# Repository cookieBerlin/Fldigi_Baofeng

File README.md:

# Fldigi_Baofeng
Interface between PC and a Baofeng

Sources:
- Speaker Microphone Pin Out http://www.miklor.com/COM/UV_Technical.php
- NBEMS using a Baofeng UV-5R on the cheap http://imnota.xenopho.be/2013/09/nbems-using-baofeng-uv-5r-on-cheap.html
- schematic of my simple audio interface for the UV-3R and UV-5R https://www.nonstopsystems.com/radio/hellschreiber-software.htm

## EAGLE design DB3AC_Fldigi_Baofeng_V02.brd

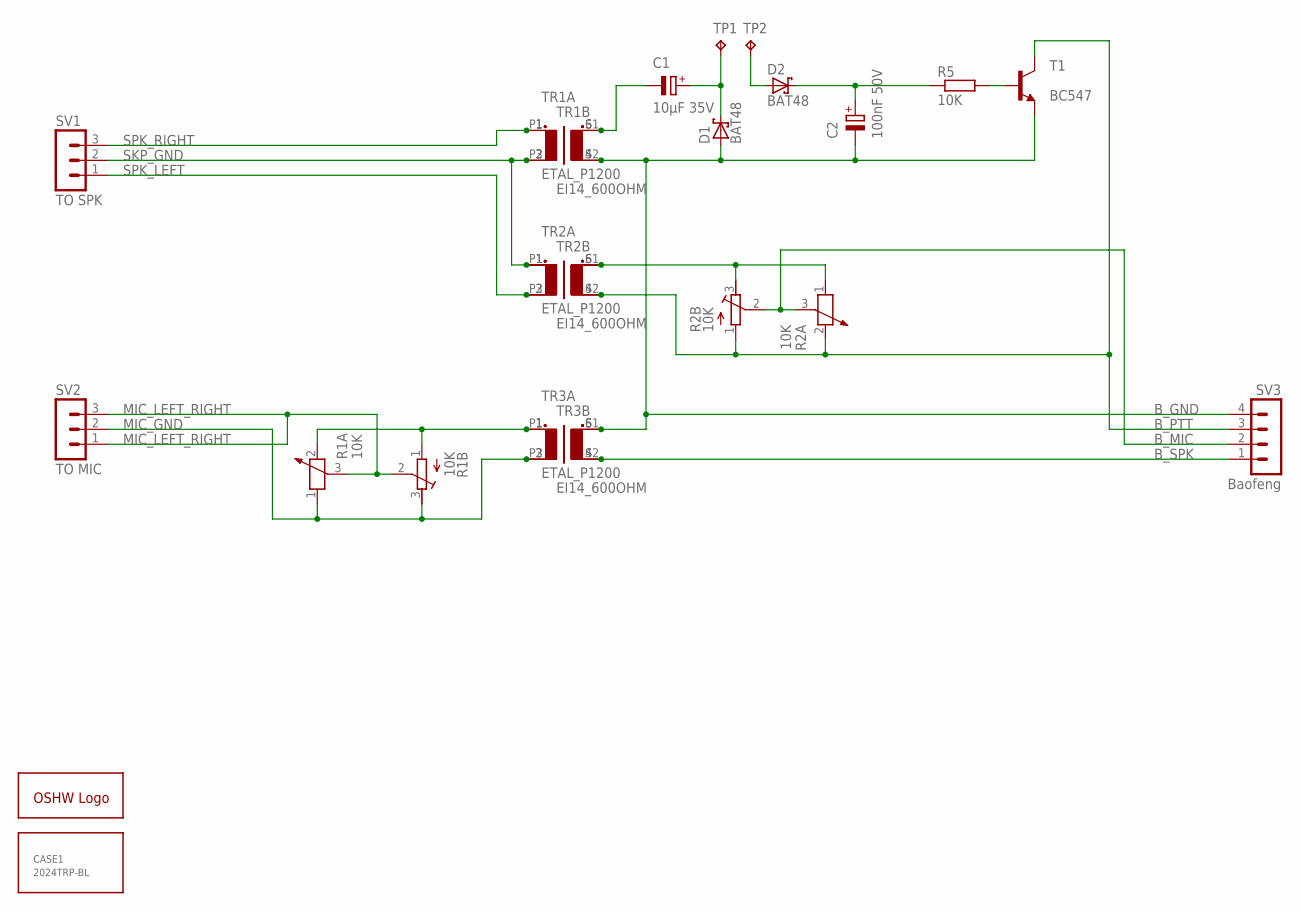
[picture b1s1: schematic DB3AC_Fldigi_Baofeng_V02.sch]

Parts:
C1: 10µF 35V; E2,5-7
C2: 100nF 50V; E2,5-7
CASE1: 2024TRP-BL; 2024
D1, D2: BAT48; DO35-10
GOLD_ORB_SM1: OSHWLOGOLOGO8MM; OSHW_8MM
R1A, R2A: 10K; PT-10
R1B, R2B: 10K; RTRIM3339P
R5: 10K; 0204/7
SV1: TO SPK; MA03-1
SV2: TO MIC; MA03-1
SV3: Baofeng; MA04-1
T1: BC547; TO92-CBE
TP1, TP2: TPPAD1-13Y; P1-13Y
TR1A, TR2A, TR3A: ETAL_P1200
TR1B, TR2B, TR3B: EI14_600OHM; EI14

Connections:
B_GND: C2.-, D1.A, SV3.4, T1.E, TR1A.4 (S2), TR1B.S2, TR3A.6 (S1), TR3B.S1
B_MIC: R2A.3, R2B.2 (S), SV3.2
B_PTT: R2A.2, R2B.1 (A), SV3.3, T1.C, TR2A.4 (S2), TR2B.S2
B_SPK: SV3.1, TR3A.4 (S2), TR3B.S2
MIC_GND: R1A.1, R1B.3 (E), SV2.2, TR3A.3 (P2), TR3B.P2
MIC_LEFT_RIGHT: R1A.3, R1B.2 (S), SV2.1, SV2.3
unnamed: R1A.2, R1B.1 (A), TR3A.1, TR3B.P1
unnamed: D2.A, TP2.TP
unnamed: R2A.1, R2B.3 (E), TR2A.6 (S1), TR2B.S1
unnamed: C1.-, TR1A.6 (S1), TR1B.S1
unnamed: R5.2, T1.B
unnamed: C1.+, D1.C, TP1.TP
unnamed: C2.+, D2.C, R5.1
SKP_GND: SV1.2, TR1A.3 (P2), TR1B.P2, TR2A.1, TR2B.P1
SPK_LEFT: SV1.1, TR2A.3 (P2), TR2B.P2
SPK_RIGHT: SV1.3, TR1A.1, TR1B.P1

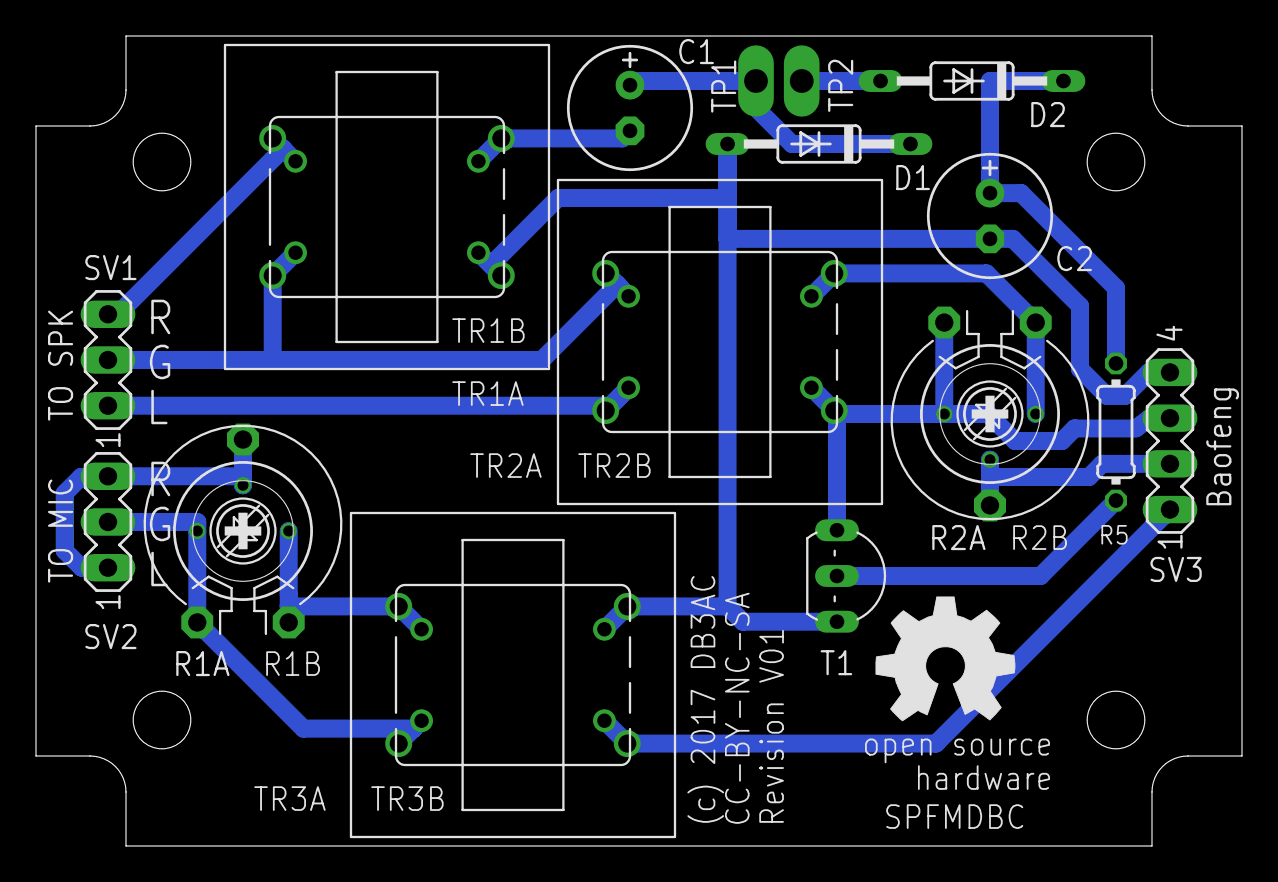
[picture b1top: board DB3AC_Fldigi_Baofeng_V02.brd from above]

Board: 2 copper layers, 67.0 x 45.0 mm, 23 parts (0 on the bottom side), 16 nets.

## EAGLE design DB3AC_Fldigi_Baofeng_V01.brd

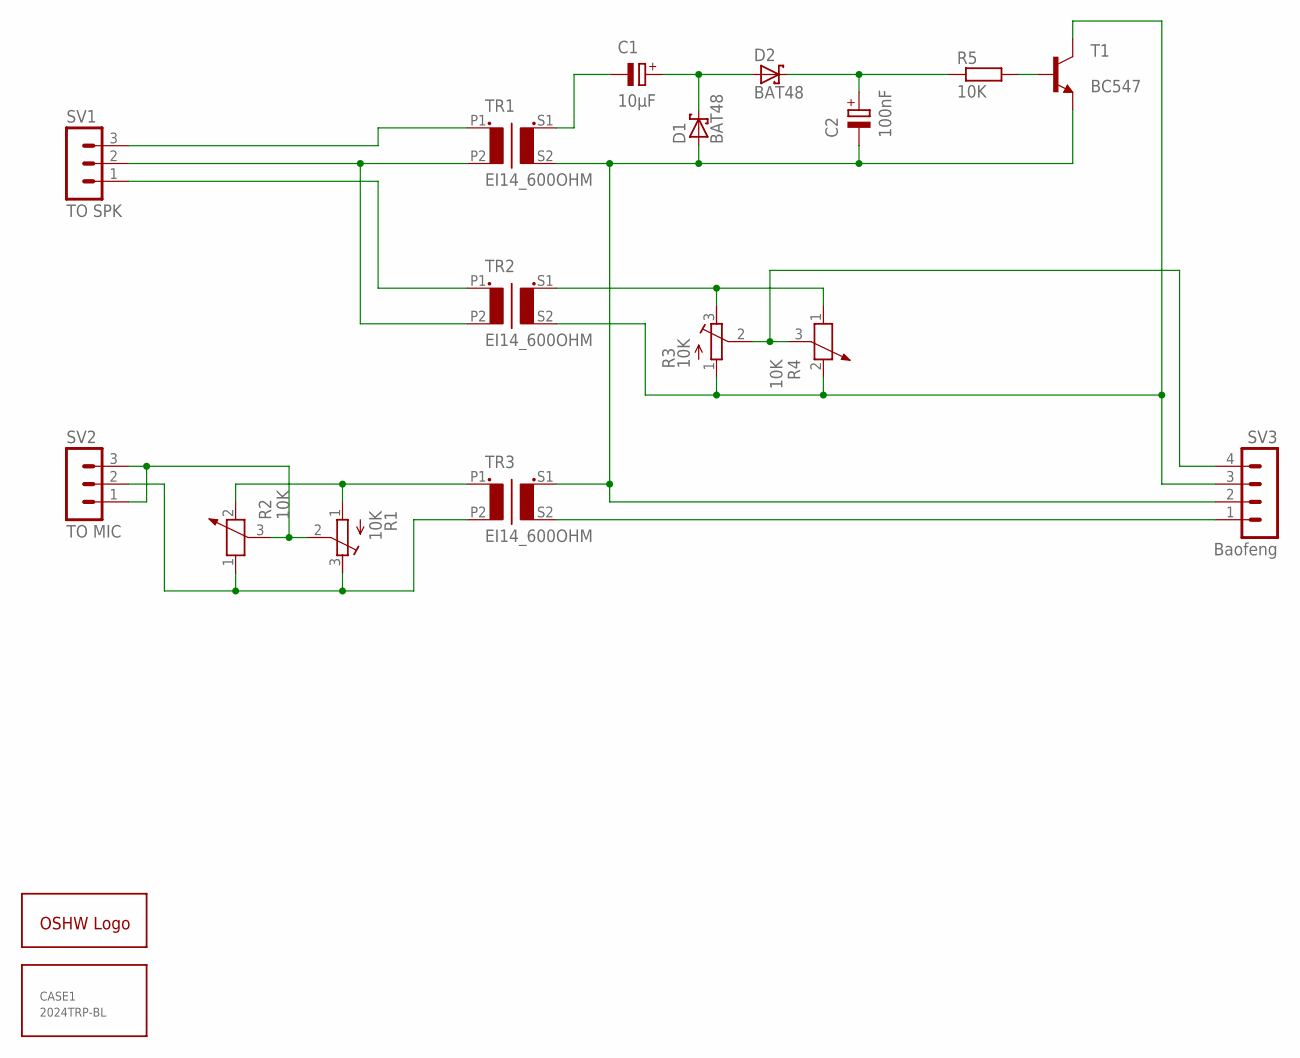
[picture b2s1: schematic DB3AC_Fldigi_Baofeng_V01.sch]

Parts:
C1: 10µF; E2,5-7
C2: 100nF; E2,5-7
CASE1: 2024TRP-BL; 2024
D1, D2: BAT48; DO35-10
GOLD_ORB_SM1: OSHWLOGOLOGO8MM; OSHW_8MM
R1, R3: 10K; RTRIM3339P
R2, R4: 10K; PT-10
R5: 10K; 0204/7
SV1: TO SPK; MA03-1
SV2: TO MIC; MA03-1
SV3: Baofeng; MA04-1
T1: BC547; TO92-CBE
TR1, TR2, TR3: EI14_600OHM; EI14

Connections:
unnamed: R1.1 (A), R2.2, TR3.P1
unnamed: R1.2 (S), R2.3, SV2.1, SV2.3
unnamed: R3.1 (A), R4.2, SV3.3, T1.C, TR2.S2
unnamed: R3.2 (S), R4.3, SV3.4
unnamed: C2.-, D1.A, SV3.2, T1.E, TR1.S2, TR3.S1
unnamed: R3.3 (E), R4.1, TR2.S1
unnamed: SV3.1, TR3.S2
unnamed: C1.-, TR1.S1
unnamed: SV1.3, TR1.P1
unnamed: SV1.1, TR2.P1
unnamed: R5.2, T1.B
unnamed: C1.+, D1.C, D2.A
unnamed: C2.+, D2.C, R5.1
unnamed: SV1.2, TR1.P2, TR2.P2
unnamed: R1.3 (E), R2.1, SV2.2, TR3.P2

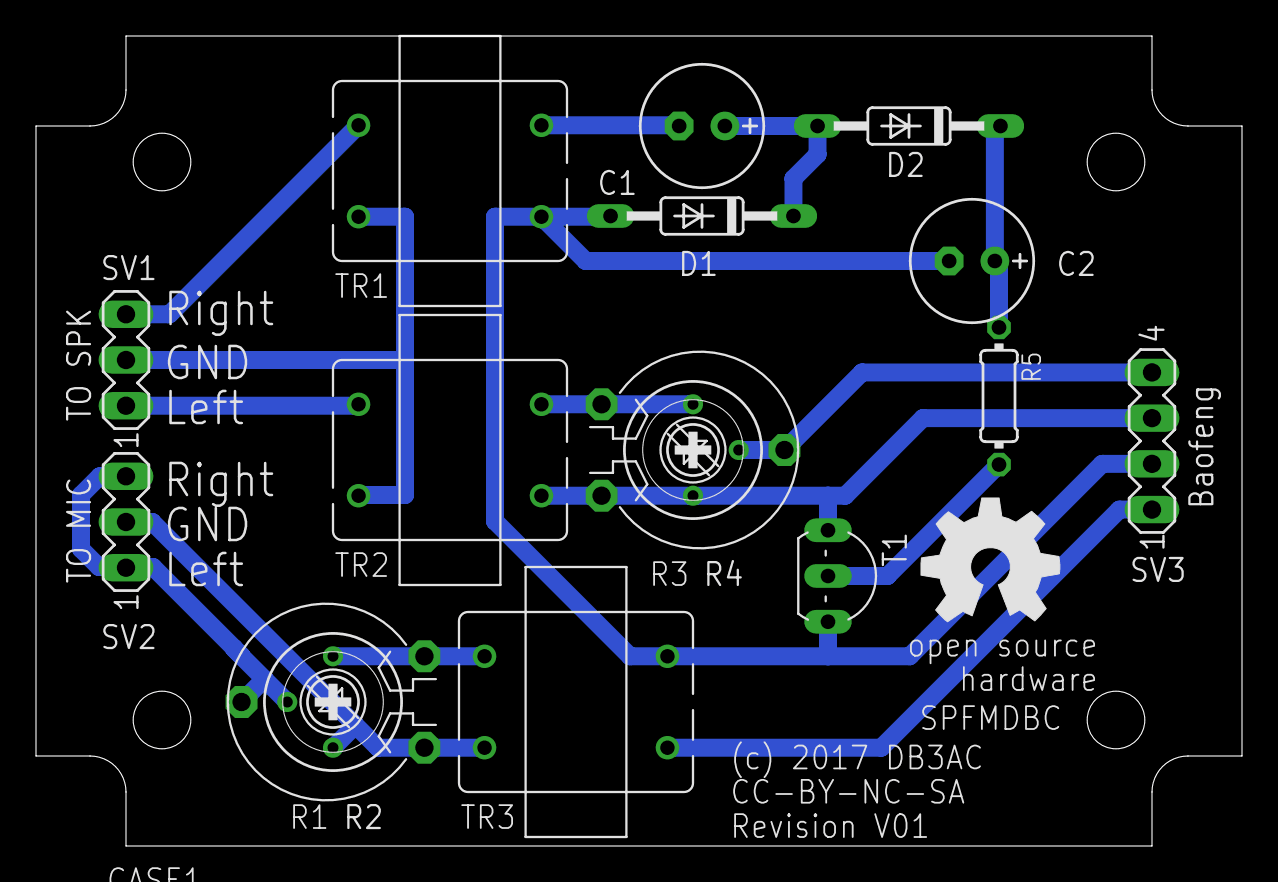
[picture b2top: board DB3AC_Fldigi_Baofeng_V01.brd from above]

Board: 2 copper layers, 67.0 x 45.0 mm, 18 parts (0 on the bottom side), 15 nets.

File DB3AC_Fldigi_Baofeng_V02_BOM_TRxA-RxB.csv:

"Qty";"Value";"Device";"Package";"Parts";"Description";"HERSTELLER";"MF";"MPN";"OC_CONRAD";"OC_FARNELL";"OC_NEWARK";"OC_SEGOR";"TP_SIGNAL_NAME";
"1";"100nF 50V";"CPOL-EUE2.5-7";"E2,5-7";"C2";"POLARIZED CAPACITOR, European symbol";"";"";"";"";"";"";"";"";
"1";"10K";"R-EU_0204/7";"0204/7";"R5";"RESISTOR, European symbol";"";"";"";"";"";"";"";"";
"2";"10K";"R-TRIMM3339P";"RTRIM3339P";"R1B, R2B";"Trimm resistor";"";"";"";"";"";"";"";"";
"1";"10µF 35V";"CPOL-EUE2.5-7";"E2,5-7";"C1";"POLARIZED CAPACITOR, European symbol";"";"";"";"";"";"";"";"";
"1";"2024TRP-BL";"2024TRP-BL";"2024";"CASE1";"Link: http://strapubox.de/modules/uploadmanager11/admin/index.php?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";"";"";"";"525967";"";"";"2024 trp-bl";"";
"2";"BAT48";"BAT42";"DO35-10";"D1, D2";"DIODE";"";"";"";"";"";"";"";"";
"1";"BC547";"BC547-NPN-TO92-CBE";"TO92-CBE";"T1";"NPN Transistror";"";"";"";"";"";"";"";"";
"1";"Baofeng";"MA04-1";"MA04-1";"SV3";"PIN HEADER";"";"";"";"";"unknown";"unknown";"";"";
"3";"ETAL_P1200";"ETAL_P1200";"ETAL_P1200";"TR1A, TR2A, TR3A";"P1200 -  Trenntransformator, Anpassungsübertrager, 100 µA";"ETAL";"";"P1200";"";"1130832";"";"";"";
"1";"OSHWLOGOLOGO8MM";"OSHWLOGOLOGO8MM";"OSHW_8MM";"GOLD_ORB_SM1";"The OSHW logo for PCB layout";"";"";"";"";"";"";"";"";
"1";"TO MIC";"MA03-1";"MA03-1";"SV2";"PIN HEADER";"";"";"";"";"unknown";"unknown";"";"";
"1";"TO SPK";"MA03-1";"MA03-1";"SV1";"PIN HEADER";"";"";"";"";"unknown";"unknown";"";"";
"2";"TPPAD1-13Y";"TPPAD1-13Y";"P1-13Y";"TP1, TP2";"Test pad";"";"";"";"";"";"";"";"";

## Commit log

2017-12-04 add First Versions
2018-04-12 add BOM variants
2018-04-12 add PDF files

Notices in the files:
DB3AC_Fldigi_Baofeng_V01.brd:
(c) 2017 DB3AC
CC-BY-NC-SA
